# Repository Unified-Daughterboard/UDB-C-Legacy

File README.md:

# Unified Daughterboard Legacy C Series

# Notice
The **C3 series daughterboard has been deprecated** with the launch of the [C4 series](https://github.com/Unified-Daughterboard/UDB-C).  
This repository will be kept up for the sake of the ability to maintain legacy keyboards, but the legacy C3 daughterboard is now not-for-new-designs - **please use the newer daughterboards instead for new keyboard projects**.  
  
In addition, documentation has moved to the new [documentation site](https://unified-daughterboard.github.io/).  

---

## Original Readme

## Introduction
The Unified Daughterboard Project is an attempt by leading designers in the mechanical keyboard community to standardize the USB daughterboards used for their custom mechanical keyboard projects. It has initially been envisioned by users ai03, Wilba, Hineybush, Xelus, Xondat, aeryxz and Maximillian.

The main characteristic of this daughterboard is to integrate a USB Type C connector and the needed circuitry for USB2.0 operation in a small PCB that can be screwed to a keyboard chassis; this significantly simplifies the assembly and design of the main circuit board.

## C3 version

In its current version, C3, this daughterboard features:

* ESD (Electrostatic Discharge) protection on the data lines of the USB connector through a specialized chip;
* Overcurrent protection through a PTC fuse;
* Overvoltage protection through a bidirectional TVS diode;
* Shielding noise decoupling capabilities through a ferrite bead;
* Single-path grounding of the metallic chassis to which the daughterboard is attached.

Adittionally, the C3 version is backwards compatible with both C1 and C2 versions since it has the same dimensions and uses the same screw hole sizes and positions, so keyboards designed using the past versions should also support C3.

## Detailed features

The figure below shows the schematic of the C3 version.

* U1 is the ESD protection for the USB data lines. It is a ultra-fast, low-capacitance chip specifically designed for USB type C connectors. When one of the data lines presents a sudden voltage spike, this chip promptly grounds it -- avoiding damage to the circuit that uses these lines;
* Resistors R1 and R2 are the CC resistors needed for operation of the USB Type C. These resistors are used by the USB host to know that the daughterboard is a downstream device and which side of the USBC connector is connected;
* Fuse F1 provides overcurrent protection. It is a PTC resettable;
* Diode D1 is a Transient Voltage Suppressor that exerpts to the power rails of the connector the same effect as the U1 chiup to data lines; when a voltge spike is detected, it shorts VCC and GND, aavoiding damage to the forward circuitry;
* Inductor L1 is a ferrite bead that presetns a very low impedance between the power ground and the signal ground in DC regimen; in high frequencies (for instance in an ESD event) it presents a very high impedance, avoiding noisy currents passing to the signal GND;
* The daughterboard features four screw holes used to fix it into a metal chassis. The top left mounting hole is shorted to the power ground signal; this means that the metal chassis of the keyboard will be grounded. However, the other three screw holes are not shorted to the power ground and are effectively isolated from that signal. This ensures that, in a discharge event emerging from the user providing charge to the system, the discharge current will have a single path through the daughterboard to the power ground; inductor L1 ensures that the discharge current is kept in the power ground plance and does not follow through to the signal ground.

## Designer/Consumer info and references
[Visit the docs](https://unified-daughterboard.github.io/)  

## Previews

## Credits
* [Gondolindrim](http://github.com/Gondolindrim)
* [ai03](http://github.com/ai03-2725)
* [Wilba](https://github.com/Wilba6582)
* [Hineybush](http://github.com/hineybush)
* [Xelus](http://github.com/Xelus22)
* Xondat
* [aeryxz](https://github.com/aeryxz)
* [Maximillian](https://github.com/Maximillian)
* [Upas](http://github.com/awkannan)

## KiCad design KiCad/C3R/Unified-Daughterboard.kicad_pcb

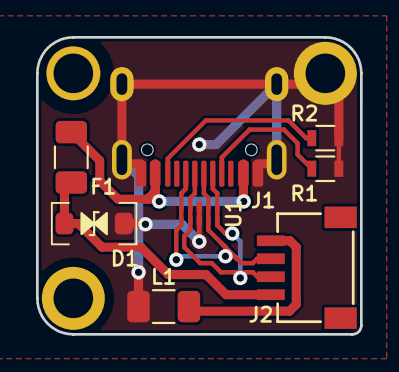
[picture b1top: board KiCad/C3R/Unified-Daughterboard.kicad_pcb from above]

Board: 2 copper layers, 18.0 x 16.5 mm, 11 parts (0 on the bottom side), 8 nets.

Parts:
D1: SMF9.0CA; D_SOD-123_Bidirectional
F1: ASMD1206-150; Fuse_1206_3216Metric
J1: TYPE-C-31-M12_13; TYPE-C-31-M-12
J2: SM04B-SRSS-TB(LF)(SN); JST-SR-4
L1: 60R@100MHz; L_1206_3216Metric
MH1, MH2, MH3: Mount-M2; Generic-Mounthole
R1, R2: 5.1k; R_0603
U1: TPD4E05U06DQAR; USON-10_2.5x1.0mm_P0.5mm

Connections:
DA+: J1.A6, J1.B6, J2.3, U1.1, U1.4, U1.7, U1.10
DA-: J1.A7, J1.B7, J2.2, U1.2, U1.5, U1.6, U1.9
GND: J2.4, L1.1
GNDPWR: D1.1, J1.A1, J1.B1, J1.S, L1.2, MH2.1, R1.2, R2.2, U1.3, U1.8
unnamed: J1.A5, R1.1
unnamed: J1.B5, R2.1
VBUS: F1.1, J1.A4, J1.B4
VCC: D1.2, F1.2, J2.1

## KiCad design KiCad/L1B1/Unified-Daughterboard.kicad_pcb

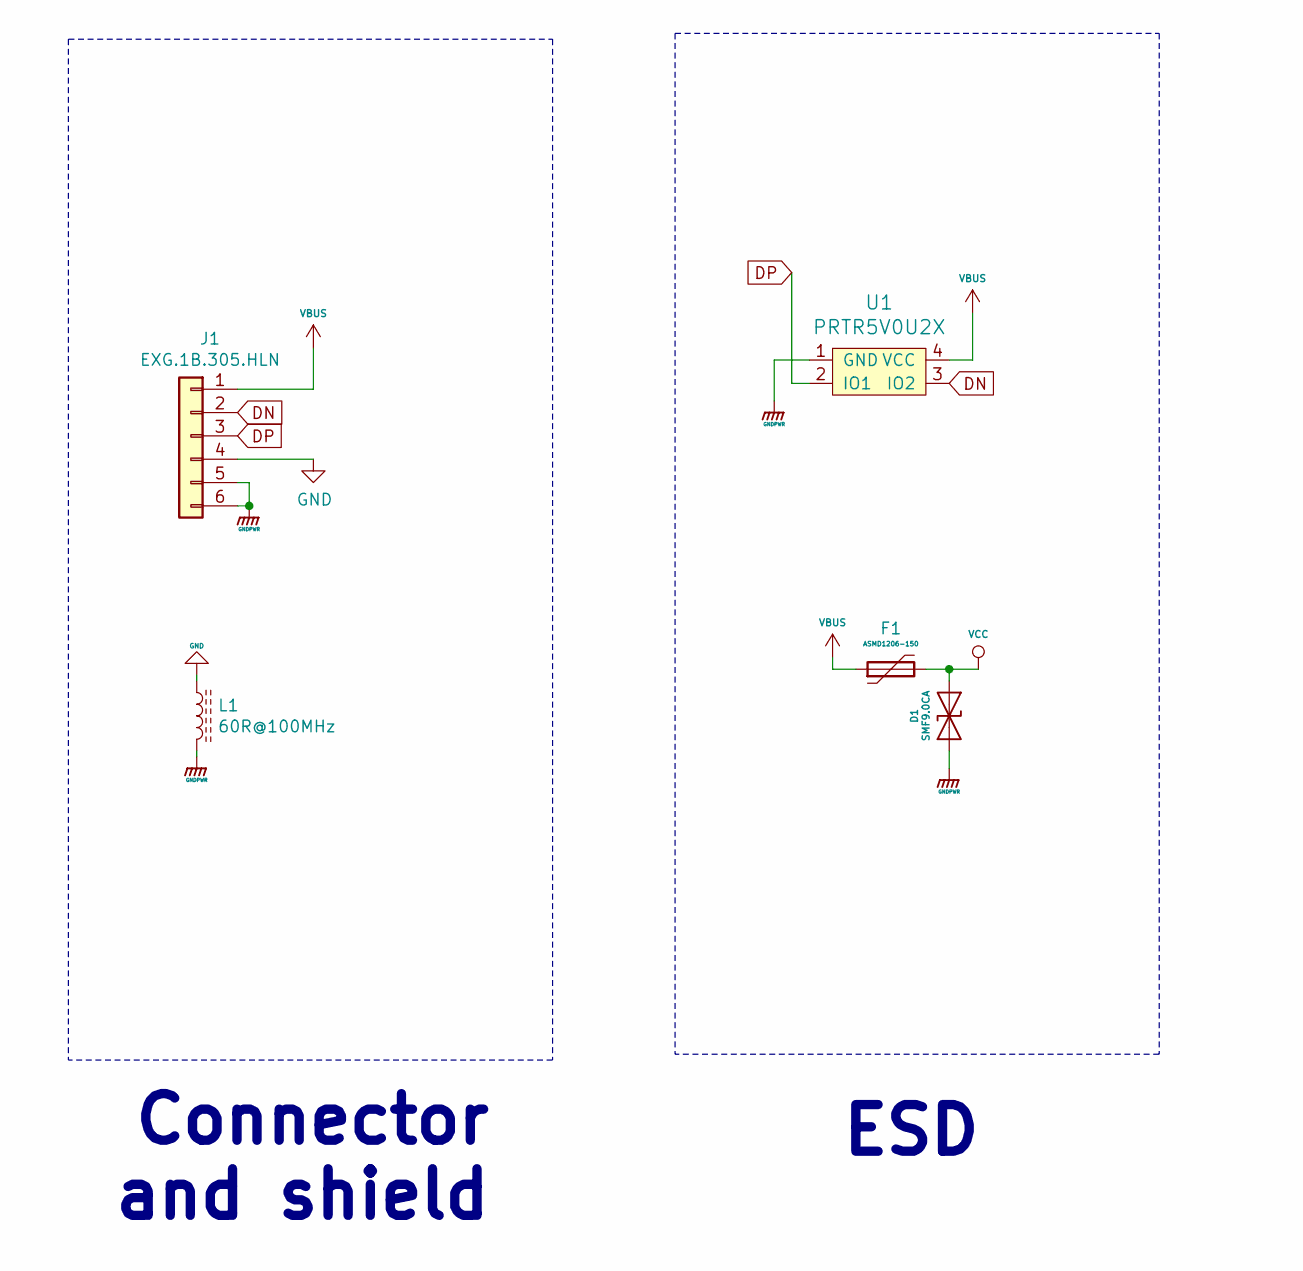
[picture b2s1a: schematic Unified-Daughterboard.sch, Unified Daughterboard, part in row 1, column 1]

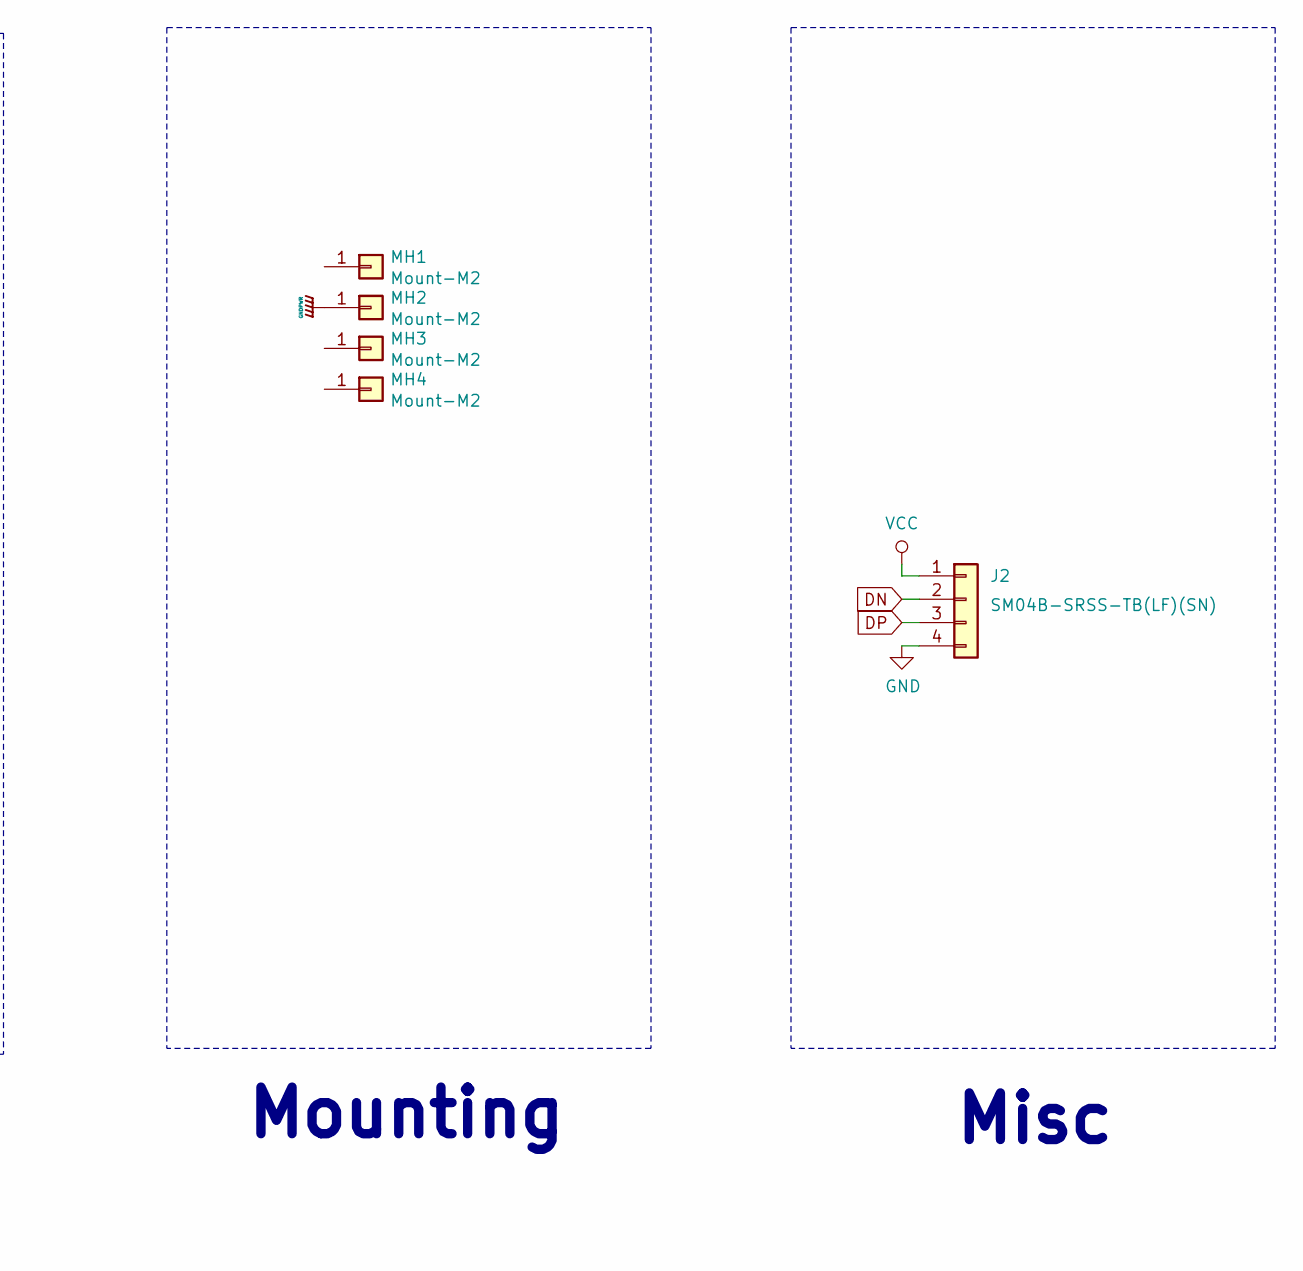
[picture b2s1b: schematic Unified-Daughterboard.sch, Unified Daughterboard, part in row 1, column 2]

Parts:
D1: SMF9.0CA; D_SOD-123_Bidirectional; Manufacturer Part No SMF9.0CA; LCSC Part No C123799
F1: ASMD1206-150; Fuse_1206_3216Metric; Manufacturer Part No ASMD1206-150; LCSC Part No C135342
J1: EXG.1B.305.HLN
J2: SM04B-SRSS-TB(LF)(SN); JST-SR-4; Manufacturer Part No SM04B-SRSS-TB(LF)(SN); LCSC Part No C160404
L1: 60R@100MHz; L_1206_3216Metric; Manufacturer Part No MLB3216-600P4A(f); LCSC Part No C33600
MH1, MH2, MH3, MH4: Mount-M2; Generic-Mounthole
U1: PRTR5V0U2X; SOT143B

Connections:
DN: J1.2, J2.2, U1.3 (IO2)
DP: J1.3, J2.3, U1.2 (IO1)
GND: J1.4, J2.4, L1.1
GNDPWR: D1.1 (A1), J1.5, J1.6, L1.2, MH2.1, U1.1 (GND)
VBUS: F1.1, J1.1, U1.4 (VCC)
VCC: D1.2 (A2), F1.2, J2.1

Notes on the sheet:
Connector and shield
ESD
Mounting
Misc

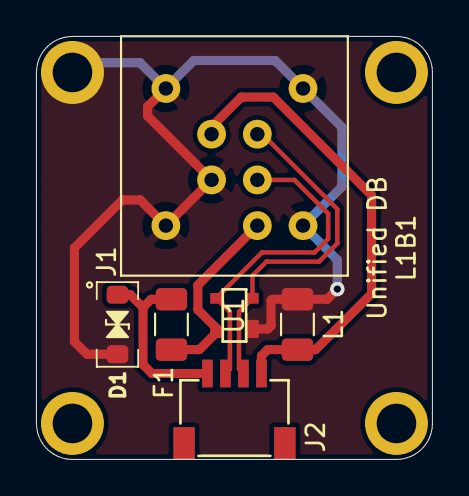
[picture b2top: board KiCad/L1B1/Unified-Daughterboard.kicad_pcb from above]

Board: 2 copper layers, 22.0 x 23.5 mm, 10 parts (0 on the bottom side), 6 nets.

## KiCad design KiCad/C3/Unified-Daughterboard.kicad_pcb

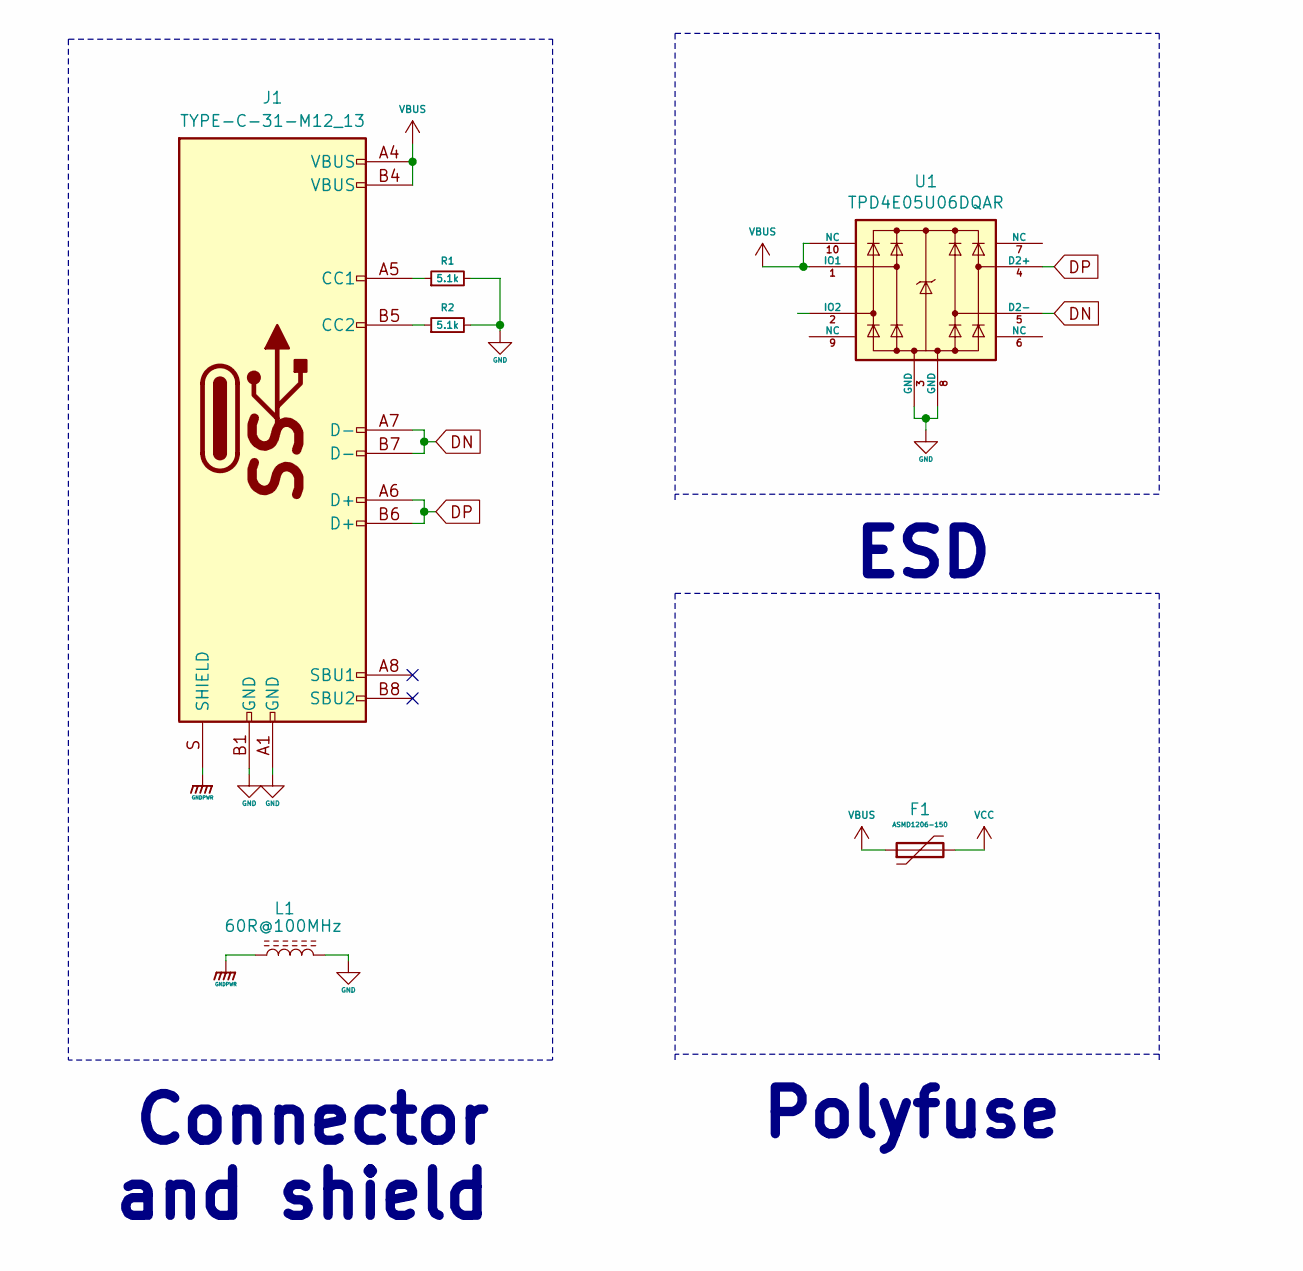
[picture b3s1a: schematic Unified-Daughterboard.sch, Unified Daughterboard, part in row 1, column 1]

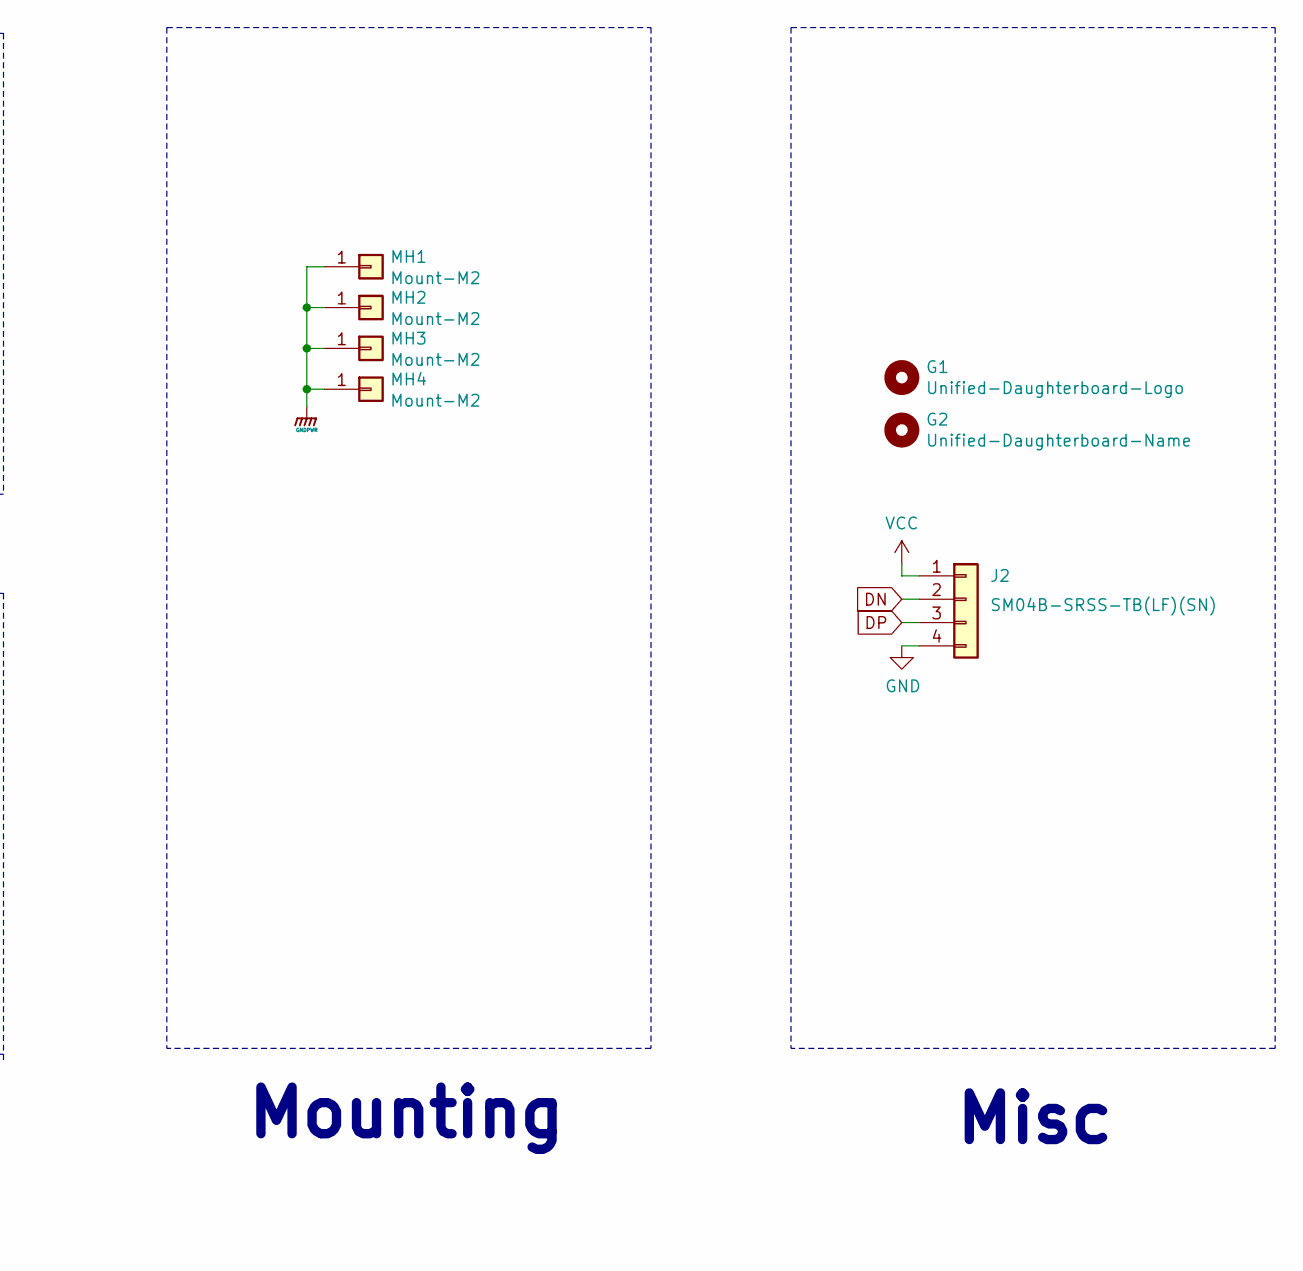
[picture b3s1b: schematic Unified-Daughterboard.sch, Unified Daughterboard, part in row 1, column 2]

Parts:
F1: ASMD1206-150; Fuse_1206_3216Metric; Manufacturer Part No ASMD1206-150; LCSC Part No C135342
G1: Unified-Daughterboard-Logo; Unified-Daughterboard-Logo.pretty
G2: Unified-Daughterboard-Name; Unified-Daughterboard-Name.pretty
J1: TYPE-C-31-M12_13; TYPE-C-31-M-12; Manufacturer Part No TYPE-C-31-M-12; LCSC Part No C165948
J2: SM04B-SRSS-TB(LF)(SN); JST-SR-4; Manufacturer Part No SM04B-SRSS-TB(LF)(SN); LCSC Part No C160404
L1: 60R@100MHz; L_1206_3216Metric; Manufacturer Part No MLB3216-600P4A(f); LCSC Part No C33600
MH1, MH2, MH3, MH4: Mount-M2; MountingHole_2.2mm_M2_ISO7380_Pad
R1, R2: 5.1k; R_0603
U1: TPD4E05U06DQAR; USON-10_2.5x1.0mm_P0.5mm; Manufacturer Part No TPD4E05U06DQAR; LCSC Part No C138714

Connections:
DN: J1.A7 (D-), J1.B7 (D-), J2.2, U1.5 (D2-)
DP: J1.A6 (D+), J1.B6 (D+), J2.3, U1.4 (D2+)
GND: J1.A1 (GND), J1.B1 (GND), J2.4, L1.2, R1.2, R2.2, U1.3 (GND), U1.8 (GND)
GNDPWR: J1.S (SHIELD), L1.1, MH1.1, MH2.1, MH3.1, MH4.1
unnamed: J1.A5 (CC1), R1.1
unnamed: J1.B5 (CC2), R2.1
VBUS: F1.1, J1.A4 (VBUS), J1.B4 (VBUS), U1.1 (IO1), U1.10 (NC)
VCC: F1.2, J2.1

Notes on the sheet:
Connector and shield
ESD
Mounting
Misc
Polyfuse

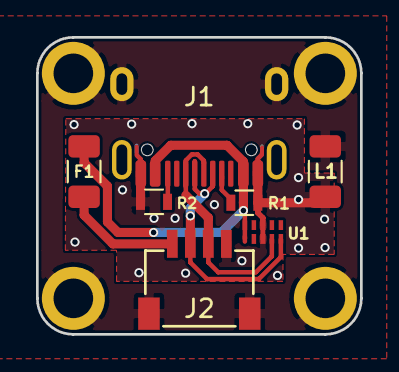
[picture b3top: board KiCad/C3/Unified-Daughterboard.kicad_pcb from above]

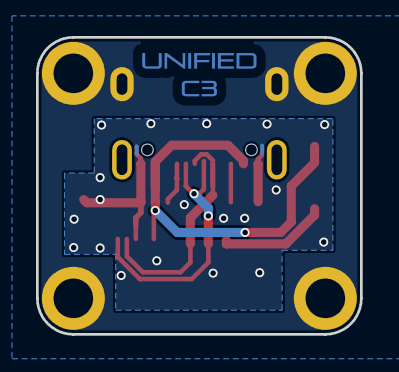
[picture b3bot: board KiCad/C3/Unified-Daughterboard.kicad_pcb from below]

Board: 2 copper layers, 18.0 x 16.5 mm, 13 parts (2 on the bottom side), 8 nets.

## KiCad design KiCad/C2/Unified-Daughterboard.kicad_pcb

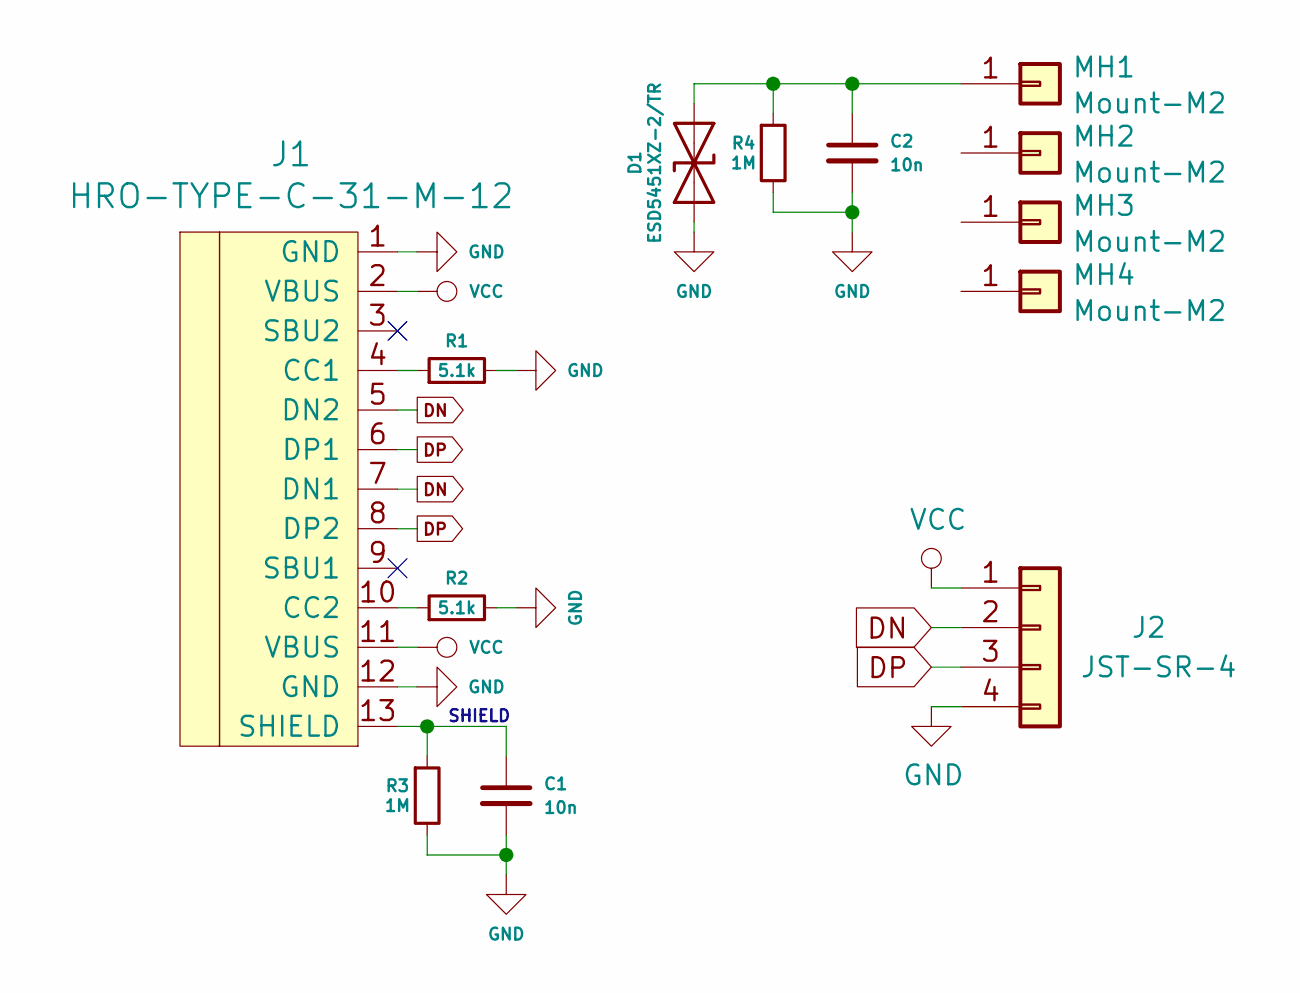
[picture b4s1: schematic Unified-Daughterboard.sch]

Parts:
C1, C2: 10n; C_0603_1608Metric
D1: ESD5451XZ-2/TR; D_0603_1608Metric
J1: HRO-TYPE-C-31-M-12; HRO-TYPE-C-31-M-12-Assembly
J2: JST-SR-4
MH1, MH2, MH3, MH4: Mount-M2; Generic-Mounthole
R1, R2: 5.1k; R_0603
R3, R4: 1M; R_0603_1608Metric

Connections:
D+: J1.6 (DP1), J1.8 (DP2), J2.3
D-: J1.5 (DN2), J1.7 (DN1), J2.2
GND: C1.2, C2.2, D1.1 (A1), J1.1 (GND), J1.12 (GND), J2.4, R1.2, R2.2, R3.2, R4.2
unnamed: C1.1, J1.13 (SHIELD), R3.1
unnamed: C2.1, D1.2 (A2), MH1.1, R4.1
unnamed: J1.4 (CC1), R1.1
unnamed: J1.10 (CC2), R2.1
VCC: J1.2 (VBUS), J1.11 (VBUS), J2.1

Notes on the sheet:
SHIELD

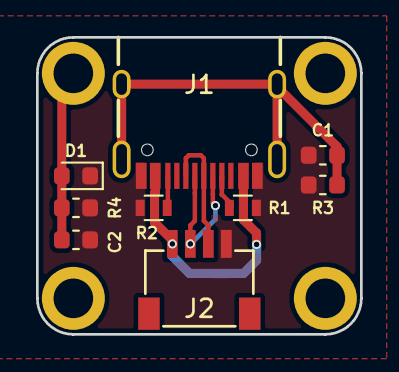
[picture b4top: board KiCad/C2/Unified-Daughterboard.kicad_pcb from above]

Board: 2 copper layers, 18.0 x 16.5 mm, 13 parts (0 on the bottom side), 8 nets.

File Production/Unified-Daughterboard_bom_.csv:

Component,Description,Part,References,Value,Footprint,Quantity Per PCB,Datasheet
1,"JST Connector, SR series, 4 pin, 1mm pitch - SM04B-SRSS-TB(LF)(SN)",Conn_01x04,J2,SM04B-SRSS-TB(LF)(SN),JST-SR-4,1,~
2,USB Type-C Connector HRO TYPE-C-31-M-12,HRO-TYPE-C-31-M-12,J1,HRO-TYPE-C-31-M-12,HRO-TYPE-C-31-M-12-Assembly,1,
3,"Resistor, small symbol",R_Small,R1 R2,5.1k,R_0603,2,~
,,,,,,,
,,,,,,,
,,,,,,,
,,,,,,,
,,,,,,,
Component Groups:,3,,,,,,
Component Count:,4,,,,,,
Fitted Components:,4,,,,,,
Number of PCBs:,1,,,,,,
Total components:,4,,,,,,
Schematic Version:,,,,,,,
Schematic Date:,,,,,,,
BoM Date:,3/19/2019 21:51,,,,,,
Schematic Source:,,,,,,,
KiCad Version:,Eeschema (5.0.2)-1,,,,,,

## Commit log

2019-03-20 Build the daughterboard
2019-03-20 Update submodules
2019-03-20 Add renders
2019-03-20 Generate production files
2019-03-20 Add designer resources
2019-03-20 Begin move files
2019-03-20 Move submodules
2019-08-28 Update with elecrow production data
2019-08-28 Add some designer info
2019-08-28 Add screw info
2020-01-08 Organized schematic
2020-01-08 Improved grounding and shielding
2020-01-08 Move from C1 folder to C2
2020-01-08 Add design resources and images for C2
2020-01-08 Update README images problems
2020-01-29 Solved format issue with C2 BoM
2020-03-22 Initial proposed version
2020-03-22 Fixed README links
2020-03-23 Detailed schematic and features in README
2020-03-23 Fix schematic size in readme
2020-03-23 Solve star logo potential overflow
2020-03-30 Update 3D model
2020-03-30 Add zipped gerber and CSV position file
2020-04-08 Remove outdated files
2020-04-18 Remove C2 source to avoid confusion; repair C3 BOM
2020-05-02 Remove capacitors from BoM and re-link separated pour
2020-05-03 Update gerber
2020-06-26 Edit PCB file to be able to open in KiCAD 5.1.4
2020-07-02 Add cable reference
2020-07-02 Add cable images here as well
2020-07-02 Repair 3D model for resistor
2020-07-09 various optimizations to schematic and layout
2020-10-17 Added cable drawings with a fillable fields
2020-10-17 Added "modified by" field in the title block
2021-04-14 Begin work
2021-04-14 Make the db
2021-12-06 Save temp
2021-12-06 Add lib as submod
2021-12-06 Progress
2022-05-09 Create prod data
2022-05-09 Make prod data
2022-05-09 Correct JLC data
